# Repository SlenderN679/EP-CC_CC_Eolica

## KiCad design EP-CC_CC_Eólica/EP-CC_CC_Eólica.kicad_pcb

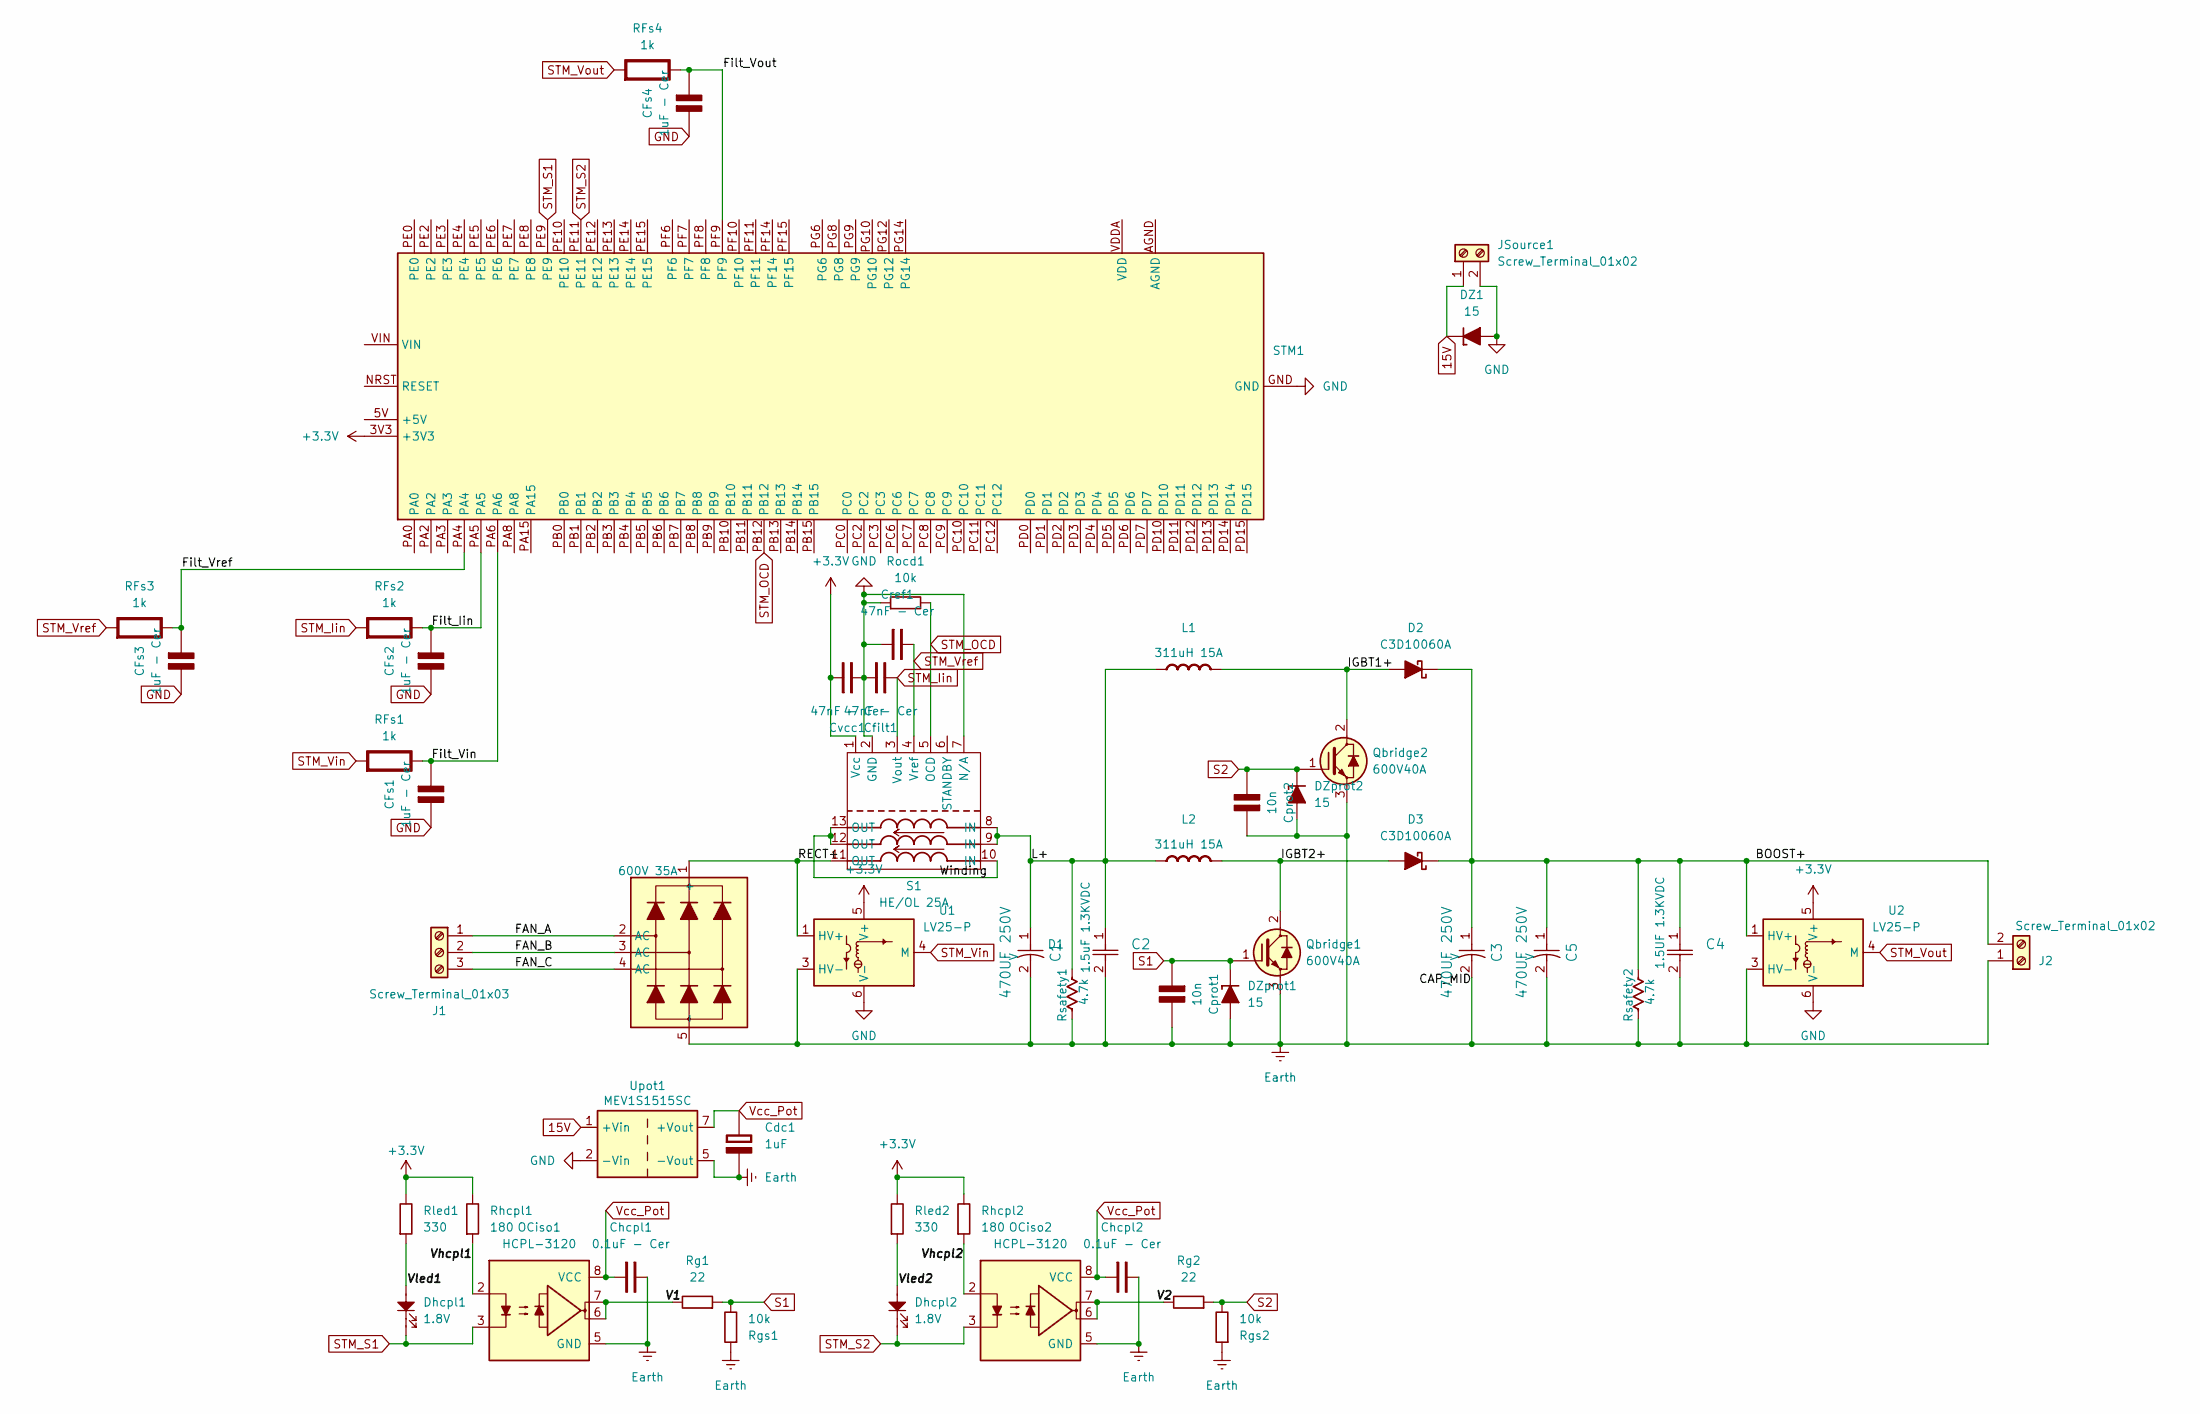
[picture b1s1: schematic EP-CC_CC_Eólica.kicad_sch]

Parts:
C1, C3, C5: 470UF 250V; LGW2E471MELZ40; Rating V
C2: 1.5uF 1.3KVDC; CAP_B32774D1155K000_TDK
C4: 1.5UF 1.3KVDC; CAP_B32774D1155K000_TDK
CFs1, CFs2, CFs3, CFs4: 1uF - Cer; C_Disc_D7.5mm_W4.4mm_P5.00mm; Rating V
Cdc1: 1uF; CP_Radial_D5.0mm_P2.00mm; Rating V
Cfilt1: 47nF - Cer; C_Disc_D5.1mm_W3.2mm_P5.00mm
Chcpl1, Chcpl2: 0.1uF - Cer; C_Disc_D5.1mm_W3.2mm_P5.00mm
Cprot1, Cprot2: 10n; C_Disc_D6.0mm_W2.5mm_P5.00mm; Rating V
Cref1: 47nF - Cer; C_Disc_D5.1mm_W3.2mm_P5.00mm
Cvcc1: 47nF - Cer; C_Disc_D5.1mm_W3.2mm_P5.00mm
D1: 600V 35A; VS-36MT160
D2, D3: C3D10060A; TO-220-2_Vertical_KA
DZ1: 15; D_DO-27_P5.08mm_Vertical_AnodeUp
DZprot1, DZprot2: 15; D_DO-34_SOD68_P10.16mm_Horizontal
Dhcpl1, Dhcpl2: 1.8V; LED_D5.0mm
J1: Screw_Terminal_01x03; PhoenixContact_SPT_2.5_3-H-5.0-EX_1x03_P5.0mm_Horizontal
J2: Screw_Terminal_01x02; PhoenixContact_SPT_2.5_2-H-5.0-EX_1x02_P5.0mm_Horizontal
JSource1: Screw_Terminal_01x02; CONN2_2604-3102_WAG
L1, L2: 311uH 15A; SHBC24W-2R1A0311V; Rating A
OCiso1, OCiso2: HCPL-3120; DIP-8_W7.62mm_LongPads
Qbridge1, Qbridge2: 600V40A; TO-220_High
RFs1, RFs2, RFs3, RFs4: 1k; R_Axial_DIN0309_L9.0mm_D3.2mm_P2.54mm_Vertical; Rating W
Rg1, Rg2: 22; R_Axial_DIN0309_L9.0mm_D3.2mm_P2.54mm_Vertical
Rgs1, Rgs2: 10k; R_Axial_DIN0309_L9.0mm_D3.2mm_P2.54mm_Vertical
Rhcpl1, Rhcpl2: 180; R_Axial_DIN0309_L9.0mm_D3.2mm_P2.54mm_Vertical
Rled1, Rled2: 330; R_Axial_DIN0309_L9.0mm_D3.2mm_P2.54mm_Vertical
Rocd1: 10k; R_Axial_DIN0309_L9.0mm_D3.2mm_P2.54mm_Vertical
Rsafety1, Rsafety2: 4.7k; TWM20J4K7E
S1: HE/OL 25A; HO 25-N_SP33-1000
STM1: ST_Morpho_and_Zio_Connectors_144_STLink
U1, U2: LV25-P; LEM_LV25-P
Upot1: MEV1S1515SC; MEV1S1505SC

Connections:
15V: DZ1.1 (K), JSource1.1, Upot1.1 (+Vin)
+3.3V: Cvcc1.2, Rhcpl1.2, Rhcpl2.2, Rled1.2, Rled2.2, S1.1 (Vcc), STM1.3V3 (+3V3), U1.5 (V+), U2.5 (V+)
/BOOST+: C3.1, C4.1, C5.1, D2.1 (K), D3.1 (K), J2.2, Rsafety2.1, U2.1 (HV+)
/FAN_A: D1.2 (AC), J1.1
/FAN_B: D1.3 (AC), J1.2
/FAN_C: D1.4 (AC), J1.3
/Filt_Iin: CFs2.1 (+), RFs2.1 (+), STM1.PA5
/Filt_Vin: CFs1.1 (+), RFs1.1 (+), STM1.PA6
/Filt_Vout: CFs4.1 (+), RFs4.1 (+), STM1.PF9
/Filt_Vref: CFs3.1 (+), RFs3.1 (+), STM1.PA4
/IGBT1+: D2.2 (A), L1.2 (-), Qbridge2.2 (C)
/IGBT2+: D3.2 (A), L2.2 (-), Qbridge1.2 (C)
/L+: C1.1, C2.1, L1.1 (+), L2.1 (+), Rsafety1.1, S1.8 (IN), S1.9 (IN)
/RECT+: D1.1 (+), S1.11 (OUT), U1.1 (HV+)
/V1: OCiso1.6, OCiso1.7, Rg1.2
/V2: OCiso2.6, OCiso2.7, Rg2.2
/Vhcpl1: OCiso1.2, Rhcpl1.1
/Vhcpl2: OCiso2.2, Rhcpl2.1
/Vled1: Dhcpl1.2, Rled1.1
/Vled2: Dhcpl2.2, Rled2.1
/Winding: S1.10 (IN), S1.12 (OUT), S1.13 (OUT)
Earth: C1.2, C2.2, C3.2, C4.2, C5.2, Cdc1.2 (-), Chcpl1.2, Chcpl2.2, Cprot1.2 (-), Cprot2.2 (-), D1.5 (-), DZprot1.2 (A), DZprot2.2 (A), J2.1, OCiso1.5 (GND), OCiso2.5 (GND), Qbridge1.3 (E), Qbridge2.3 (E), Rgs1.1, Rgs2.1, Rsafety1.2, Rsafety2.2, U1.3 (HV-), U2.3 (HV-), Upot1.5 (-Vout)
GND: CFs1.2 (-), CFs2.2 (-), CFs3.2 (-), CFs4.2 (-), Cfilt1.2, Cref1.2, Cvcc1.1, DZ1.2 (A), JSource1.2, Rocd1.1, S1.2 (GND), S1.7 (N/A), STM1.GND, U1.6 (V-), U2.6 (V-), Upot1.2 (-Vin)
S1: Cprot1.1 (+), DZprot1.1 (K), Qbridge1.1 (G), Rg1.1, Rgs1.2
S2: Cprot2.1 (+), DZprot2.1 (K), Qbridge2.1 (G), Rg2.1, Rgs2.2
STM_Iin: Cfilt1.1, RFs2.2 (-), S1.3 (Vout)
STM_OCD: Rocd1.2, S1.5 (OCD), STM1.PB12
STM_S1: Dhcpl1.1, OCiso1.3, STM1.PE9
STM_S2: Dhcpl2.1, OCiso2.3, STM1.PE11
STM_Vin: RFs1.2 (-), U1.4 (M)
STM_Vout: RFs4.2 (-), U2.4 (M)
STM_Vref: Cref1.1, RFs3.2 (-), S1.4 (Vref)
Vcc_Pot: Cdc1.1 (+), Chcpl1.1, Chcpl2.1, OCiso1.8 (VCC), OCiso2.8 (VCC), Upot1.7 (+Vout)

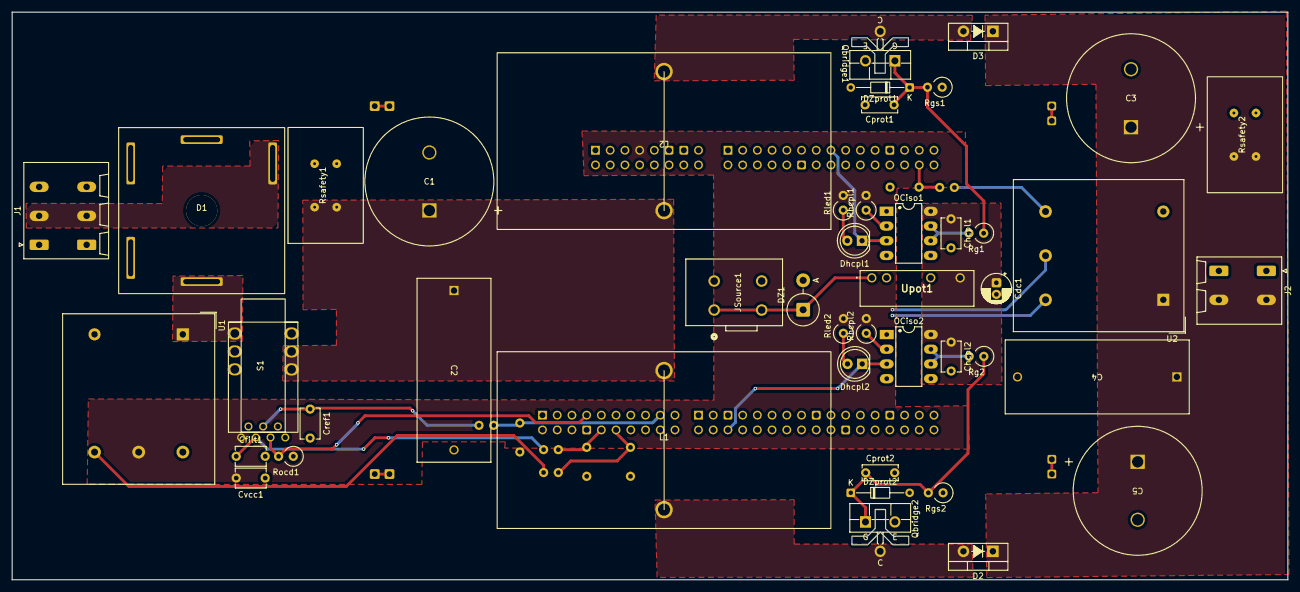
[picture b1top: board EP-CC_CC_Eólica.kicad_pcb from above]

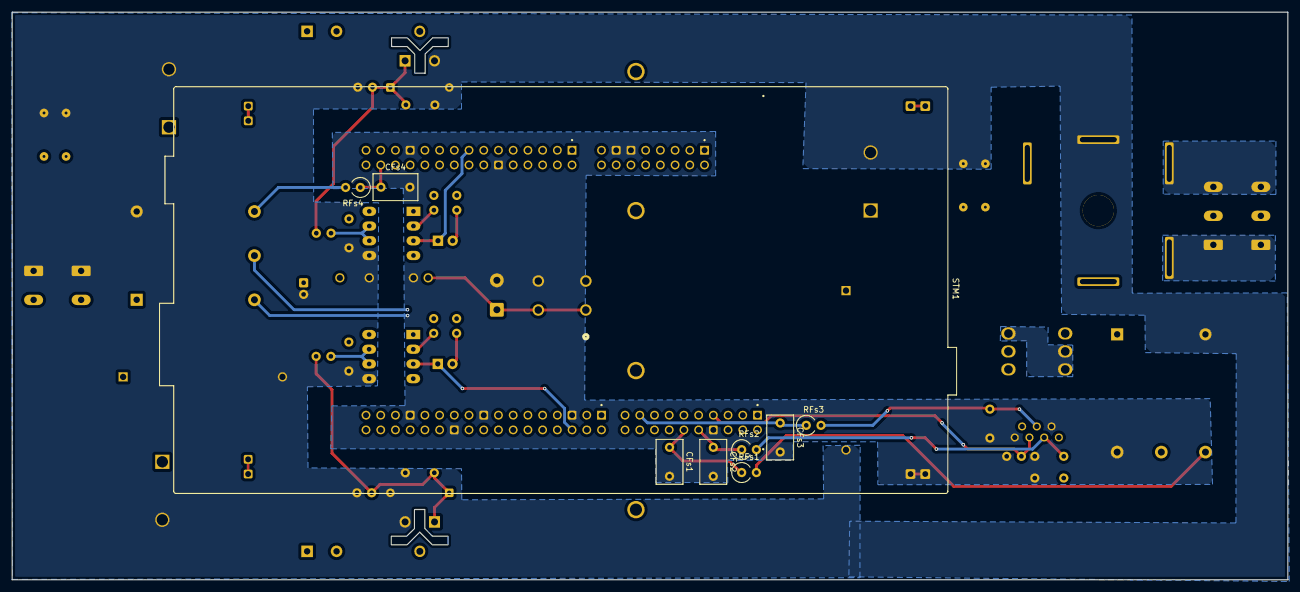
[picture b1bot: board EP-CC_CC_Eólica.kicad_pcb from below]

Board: 2 copper layers, 220.1 x 98.0 mm, 54 parts (9 on the bottom side), 33 nets.

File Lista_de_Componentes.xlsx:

Reference | Value | Qty
Condensador eletrolítico pot. | 470uF 200V | 2
Condensador de filme pot. | 1.5uF 1.3KVDC | 2
Condensador eletrolítico | 1uF | 1
Condensador de ceramica | 47nF / 0.1uF / 10n | 7
Ponte retificadora trifásica | 600V 35A | 1
Díodo de potência | C3D10060A | 2
Leds de sinalização | 1.8V | 2
Díodo de Zener | 15 | 3
Conector | Lever Terminal Block | 3
Indutores | 311uH 15A | 2
Optocouplers | HCPL-3120 | 2
IGBT | 600V40A | 2
Resistências | 22 / 10k / 180 / 330 | 9
Resistências de descarga | 4.7k | 2
Sensor de corrente | HE/OL 25A | 1
STM32 | ~ | 1
Sensor de tensão | LV25-P | 2
Conversor CC-CC isolado | MEV1S1515SC | 1
